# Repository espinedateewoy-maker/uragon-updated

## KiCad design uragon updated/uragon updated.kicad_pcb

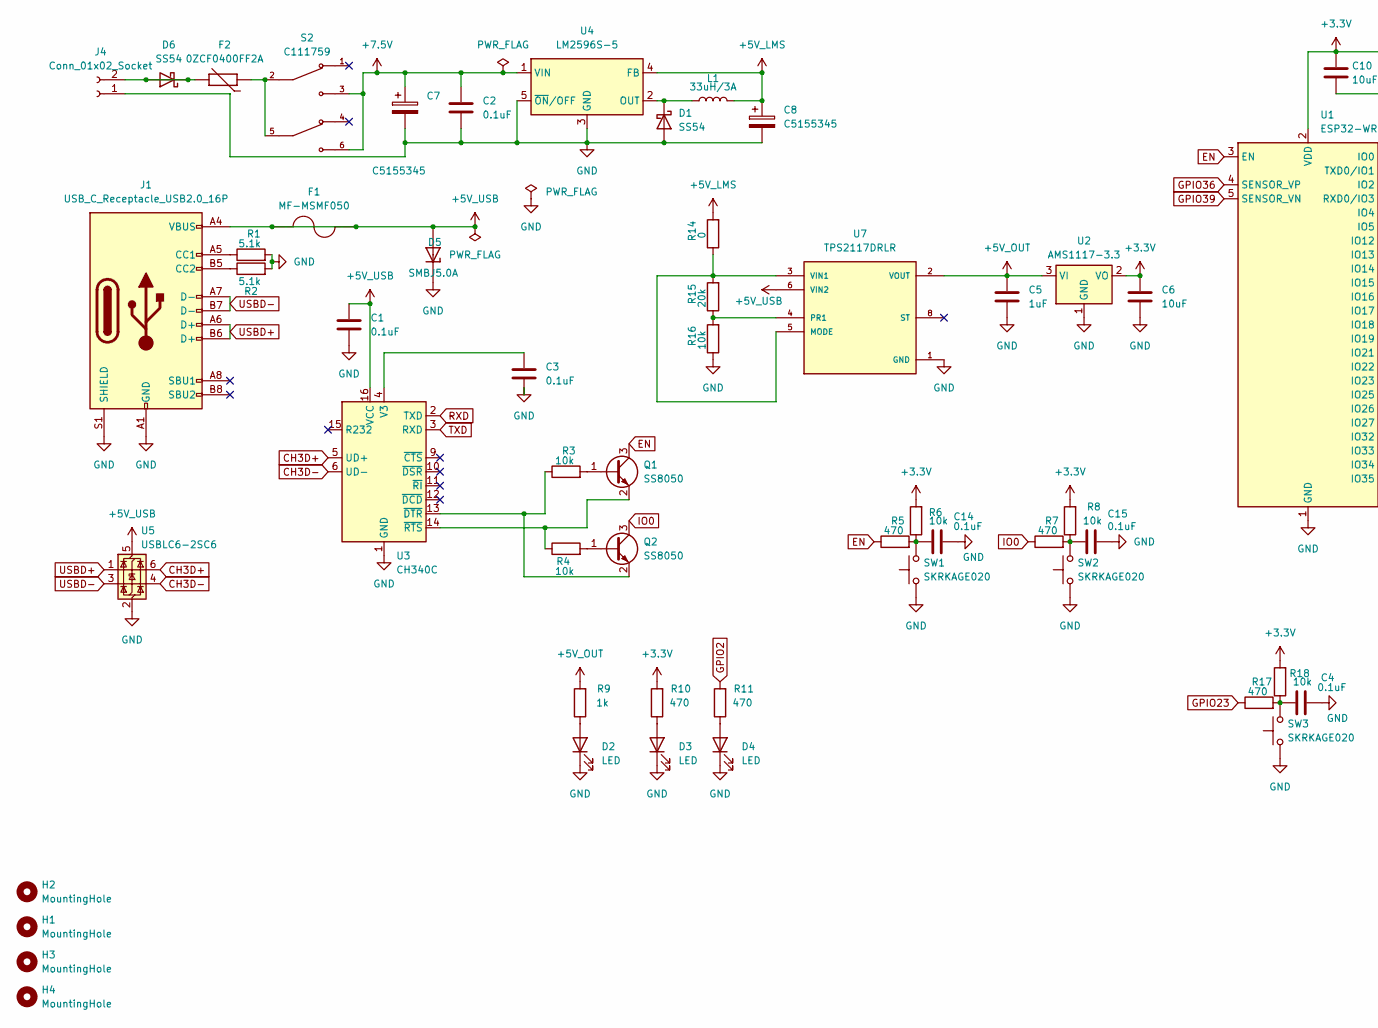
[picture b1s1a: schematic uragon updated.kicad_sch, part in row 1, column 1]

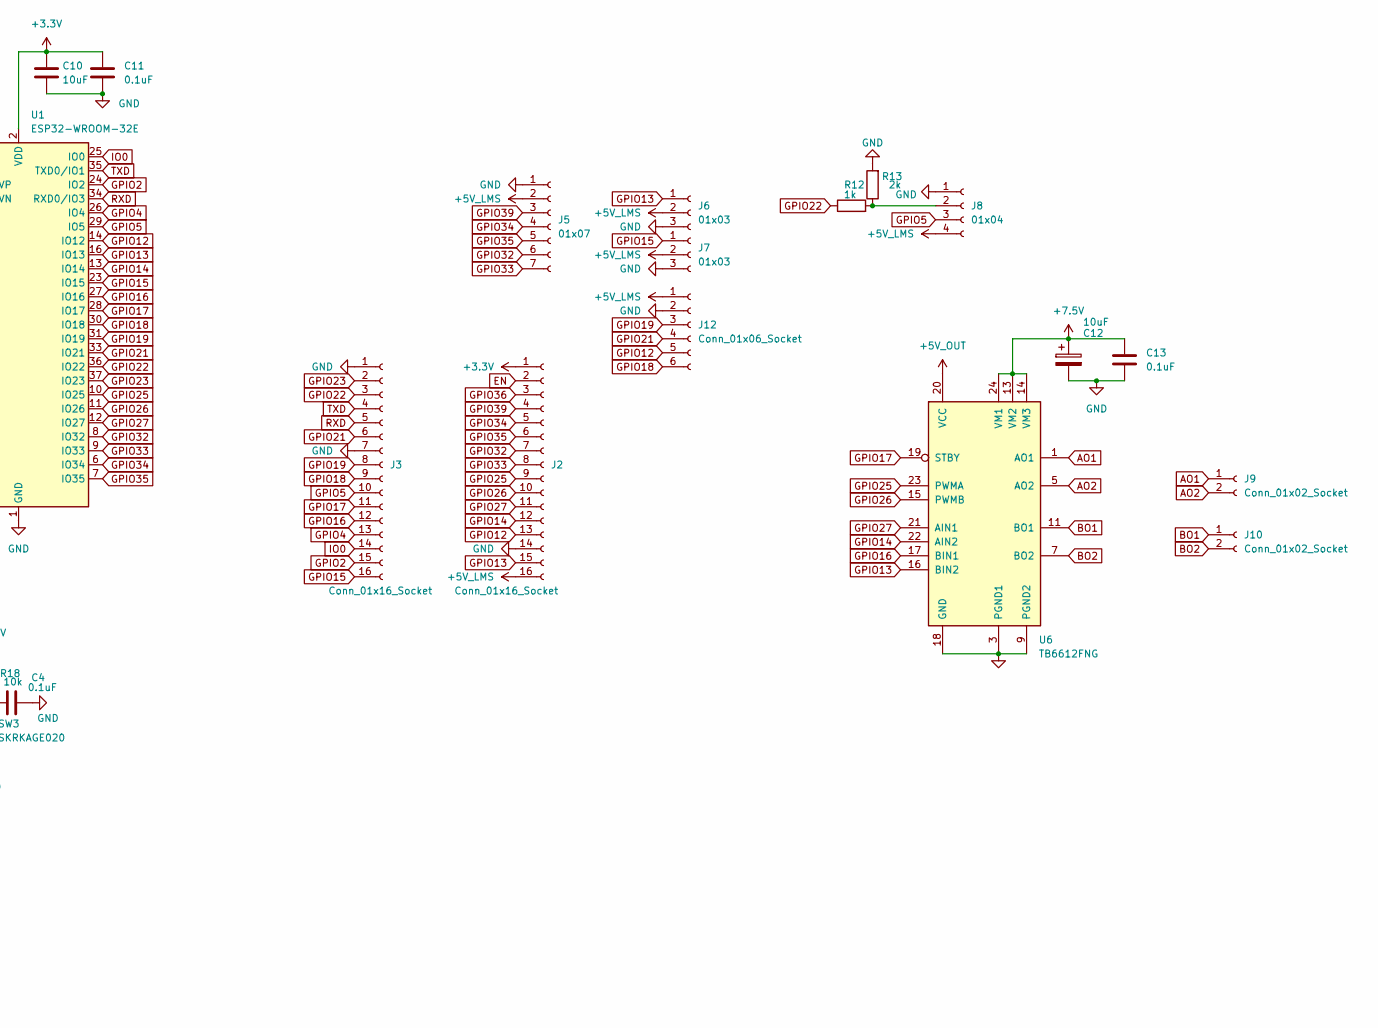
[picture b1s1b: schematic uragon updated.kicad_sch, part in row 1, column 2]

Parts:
C1, C2, C3, C4, C11, C13, C14, C15: 0.1uF; C_0805_2012Metric
C5: 1uF; C_0805_2012Metric
C6, C10: 10uF; C_0805_2012Metric
C7, C8: C5155345; CP_Elec_8x10.5
C12: 10uF; CP_EIA-6032-28_Kemet-C
D1, D6: SS54; D_SMA
D2, D3, D4: LED; LED_0805_2012Metric
D5: SMBJ5.0A; DIOM4336X265N; PARTREV F2102
F1: MF-MSMF050; FUSER_MF-MSMF050
F2: 0ZCF0400FF2A; FUSER_0ZCF0400FF2A; PARTREV Apr2023
H1, H2, H3, H4: MountingHole; MountingHole_3.2mm_M3
J1: USB_C_Receptacle_USB2.0_16P; USB_C_Receptacle_HRO_TYPE-C-31-M-12
J2, J3: Conn_01x16_Socket; PinHeader_1x16_P2.54mm_Vertical
J4: Conn_01x02_Socket; JST_PH_B2B-PH-K_1x02_P2.00mm_Vertical
J5: 01x07; PinHeader_1x07_P2.54mm_Vertical
J6, J7: 01x03; PinHeader_1x03_P2.54mm_Vertical
J8: 01x04; PinHeader_1x04_P2.54mm_Vertical
J9, J10: Conn_01x02_Socket; JST_XH_B2B-XH-A_1x02_P2.50mm_Vertical
J12: Conn_01x06_Socket; PinHeader_1x06_P2.54mm_Vertical
L1: 33uH/3A; L_12x12mm_H4.5mm
Q1, Q2: SS8050; SOT-23
R1, R2: 5.1k; R_0805_2012Metric
R3, R4, R6, R8, R16, R18: 10k; R_0805_2012Metric
R5, R7, R10, R11, R17: 470; R_0805_2012Metric
R9, R12: 1k; R_0805_2012Metric
R13: 2k; R_0805_2012Metric
R14: 0; R_0805_2012Metric
R15: 20k; R_0805_2012Metric
S2: C111759; SW_TL2230EEF100; PARTREV E
SW1, SW2, SW3: SKRKAGE020; SW_SPST_TS-1088-xR025
U1: ESP32-WROOM-32E
U2: AMS1117-3.3; SOT-223-3_TabPin2
U3: CH340C; SOIC-16_3.9x9.9mm_P1.27mm
U4: LM2596S-5; TO-263-5_TabPin3
U5: USBLC6-2SC6; SOT-23-6
U6: TB6612FNG; SSOP-24_5.3x8.2mm_P0.65mm
U7: TPS2117DRLR; SOTFL50P160X60-8N; PARTREV A; DigiKey_Part_Number 296-TPS2117DRLRCT-ND

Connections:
+3.3V: C6.1, C10.1, C11.1, J2.1, R6.2, R8.2, R10.2, R18.2, U1.2 (VDD), U2.2 (VO)
+5V_LMS: C8.1, J2.16, J5.2, J6.2, J7.2, J8.4, J12.1, L1.2, R14.2, U4.4 (FB)
+5V_OUT: C5.1, R9.2, U2.3 (VI), U6.20 (VCC), U7.2 (VOUT), U7.7 (VOUT)
+5V_USB: C1.1, D5.A, F1.1, F1.2, J1.A4 (VBUS), J1.A9 (VBUS), J1.B4 (VBUS), J1.B9 (VBUS), U3.16 (VCC), U5.5 (VBUS), U7.6 (VIN2)
+7.5V: C2.1, C7.1, C12.1, C13.1, S2.3, S2.6, U4.1 (VIN), U6.13 (VM2), U6.14 (VM3), U6.24 (VM1)
AO1: J9.1, U6.1 (AO1), U6.2 (AO1)
AO2: J9.2, U6.5 (AO2), U6.6 (AO2)
BO1: J10.1, U6.11 (BO1), U6.12 (BO1)
BO2: J10.2, U6.7 (BO2), U6.8 (BO2)
CH3D+: U3.5 (UD+), U5.6 (I/O1)
CH3D-: U3.6 (UD-), U5.4 (I/O2)
EN: J2.2, Q1.3 (C), R5.1, U1.3 (EN)
GND: C1.2, C2.2, C3.2, C4.2, C5.2, C6.2, C7.2, C8.2, C10.2, C11.2, C12.2, C13.2, C14.2, C15.2, D1.2 (A), D2.1 (K), D3.1 (K), D4.1 (K), D5.C, J1.A1 (GND), J1.A12 (GND), J1.B1 (GND), J1.B12 (GND), J1.S1 (SHIELD), J2.14, J3.1, J3.7, J4.1, J5.1, J6.3, J7.3, J8.1, J12.2, R1.2, R2.2, R13.2, R16.1, SW1.1, SW2.1, SW3.1, U1.1 (GND), U1.15 (GND), U1.38 (GND), U1.39 (GND), U2.1 (GND), U3.1 (GND), U4.3 (GND), U4.5 (~ON/OFF), U5.2 (GND), U6.3 (PGND1), U6.4 (PGND1), U6.9 (PGND2), U6.10 (PGND2), U6.18 (GND), U7.1 (GND)
GPIO2: J3.15, R11.2, U1.24 (IO2)
GPIO4: J3.13, U1.26 (IO4)
GPIO5: J3.10, J8.3, U1.29 (IO5)
GPIO12: J2.13, J12.5, U1.14 (IO12)
GPIO13: J2.15, J6.1, U1.16 (IO13), U6.16 (BIN2)
GPIO14: J2.12, U1.13 (IO14), U6.22 (AIN2)
GPIO15: J3.16, J7.1, U1.23 (IO15)
GPIO16: J3.12, U1.27 (IO16), U6.17 (BIN1)
GPIO17: J3.11, U1.28 (IO17), U6.19 (STBY)
GPIO18: J3.9, J12.6, U1.30 (IO18)
GPIO19: J3.8, J12.3, U1.31 (IO19)
GPIO21: J3.6, J12.4, U1.33 (IO21)
GPIO22: J3.3, R12.1, U1.36 (IO22)
GPIO23: J3.2, R17.1, U1.37 (IO23)
GPIO25: J2.9, U1.10 (IO25), U6.23 (PWMA)
GPIO26: J2.10, U1.11 (IO26), U6.15 (PWMB)
GPIO27: J2.11, U1.12 (IO27), U6.21 (AIN1)
GPIO32: J2.7, J5.6, U1.8 (IO32)
GPIO33: J2.8, J5.7, U1.9 (IO33)
GPIO34: J2.5, J5.4, U1.6 (IO34)
GPIO35: J2.6, J5.5, U1.7 (IO35)
GPIO36: J2.3, U1.4 (SENSOR_VP)
GPIO39: J2.4, J5.3, U1.5 (SENSOR_VN)
IO0: J3.14, Q2.3 (C), R7.1, U1.25 (IO0)
unnamed: C4.1, R17.2, R18.1, SW3.2
unnamed: C14.1, R5.2, R6.1, SW1.2
unnamed: C15.1, R7.2, R8.1, SW2.2
unnamed: D1.1 (K), L1.1, U4.2 (OUT)
unnamed: D2.2 (A), R9.1
unnamed: D3.2 (A), R10.1
unnamed: D4.2 (A), R11.1
unnamed: D6.1 (K), D6.2 (A), F2.2, J4.2
unnamed: F2.1, S2.2, S2.5
unnamed: J1.A5 (CC1), R1.1
unnamed: J1.B5 (CC2), R2.1
unnamed: J8.2, R12.2, R13.1
unnamed: Q1.1 (B), R3.2
unnamed: Q1.2 (E), R4.1, U3.14 (~RTS)
unnamed: Q2.1 (B), R4.2
unnamed: Q2.2 (E), R3.1, U3.13 (~DTR)
unnamed: C3.1, U3.4 (V3)
unnamed: R14.1, R15.2, U7.3 (VIN1), U7.5 (MODE)
unnamed: R15.1, R16.2, U7.4 (PR1)
RXD: J3.5, U1.34 (RXD0/IO3), U3.2 (TXD)
TXD: J3.4, U1.35 (TXD0/IO1), U3.3 (RXD)
USBD+: J1.A6 (D+), J1.B6 (D+), U5.1 (I/O1)
USBD-: J1.A7 (D-), J1.B7 (D-), U5.3 (I/O2)

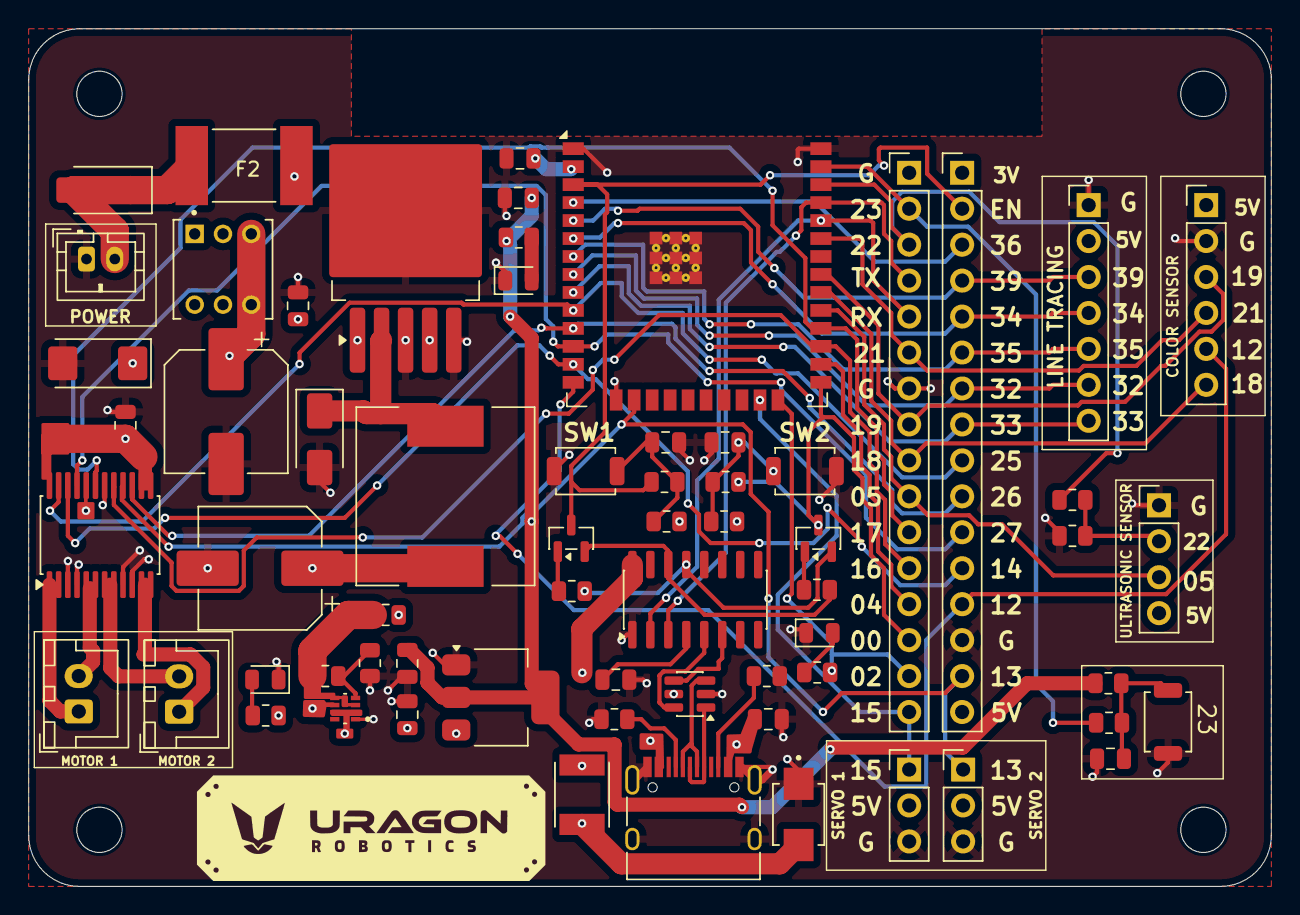
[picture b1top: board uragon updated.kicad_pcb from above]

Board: 4 copper layers, 87.8 x 60.6 mm, 69 parts (0 on the bottom side), 60 nets.

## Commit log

2026-06-23 Added diodes
2026-06-23 Added gitignore
2026-06-24 Changed the position of Diode_SMD:D_SMA
2026-06-25 Fix some connections.
2026-06-25 Fix some connections
